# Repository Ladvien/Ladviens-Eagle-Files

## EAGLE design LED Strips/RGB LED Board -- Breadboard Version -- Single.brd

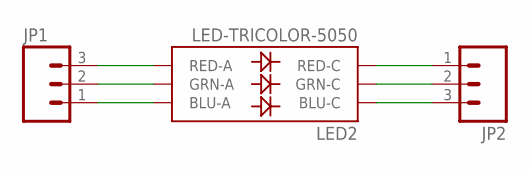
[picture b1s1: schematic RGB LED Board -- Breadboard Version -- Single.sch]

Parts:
JP1, JP2: M03PTH; 1X03
LED2: LED-TRICOLOR-5050

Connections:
unnamed: JP1.1, LED2.3 (BLU-A)
unnamed: JP1.2, LED2.1 (GRN-A)
unnamed: JP1.3, LED2.2 (RED-A)
unnamed: JP2.1, LED2.5 (RED-C)
unnamed: JP2.2, LED2.6 (GRN-C)
unnamed: JP2.3, LED2.4 (BLU-C)

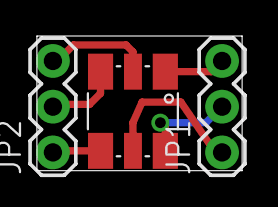
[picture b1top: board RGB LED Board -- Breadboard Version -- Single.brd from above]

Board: 2 copper layers, 11.4 x 7.5 mm, 3 parts (0 on the bottom side), 6 nets.

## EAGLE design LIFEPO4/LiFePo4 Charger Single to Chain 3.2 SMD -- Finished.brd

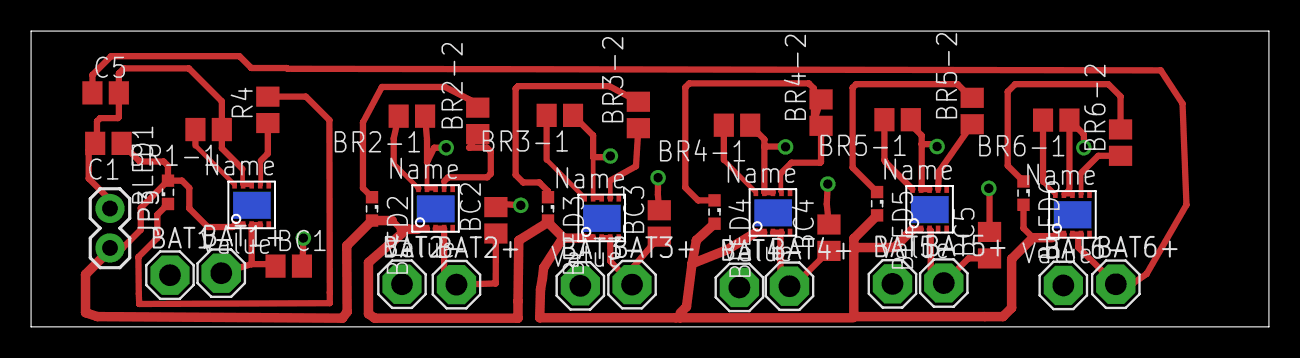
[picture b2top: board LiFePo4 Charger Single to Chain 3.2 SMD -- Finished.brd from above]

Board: 2 copper layers, 79.7 x 19.0 mm, 44 parts (0 on the bottom side), 26 nets.

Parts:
BAT1+, BAT1-, BAT2+, BAT2-, BAT3+, BAT3-, BAT4+, BAT4-, BAT5+, BAT5-, BAT6+, BAT6-: SE14
BC1, BC2, BC3, BC4, BC5: 4.7; C0805
BLED1, BLED2, BLED3, BLED4, BLED5, BLED6: 3.2v; SML0603
BR1-1, BR2-1, BR3-1, BR4-1, BR5-1, BR6-1: 1.5k; R0805
BR2-2, BR3-2, BR4-2, BR5-2, BR6-2: 1k; R0805
C1, C5: 4.7; C0805
IC2, IC4: MCP73123/223
JP3: Vraw/Grnd; 1X02
R4: 1k; R0805
U$1, U$3, U$5, U$8: MCP73123/223

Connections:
BC6: BAT6+.MP, C5.1, U$3.3, U$3.4
BR1-2: R4.1, U$1.7
GND: BAT1-.MP, BAT2-.MP, BAT3-.MP, BAT4-.MP, BAT5-.MP, BAT6-.MP, BC1.2, BC2.2, BC3.2, BC4.2, BC5.2, BR1-1.1, BR2-1.1, BR3-1.1, BR4-1.1, BR5-1.1, BR6-1.1, C1.2, C5.2, IC2.8, IC2.9, IC4.8, IC4.9, JP3.1, U$1.8, U$1.9, U$3.8, U$3.9, U$5.8, U$5.9, U$8.8, U$8.9
unnamed: BLED1.A, BLED2.A, BLED3.A, BLED4.A, BLED5.A, BLED6.A, C1.1, IC2.1, IC2.2, IC4.1, IC4.2, JP3.2, U$1.1, U$1.2, U$3.1, U$3.2, U$5.1, U$5.2, U$8.1, U$8.2
unnamed: BAT5+.MP, BC5.1, U$8.3
unnamed: BR5-1.2, U$8.10
unnamed: BLED5.C, BR5-2.2
unnamed: BR5-2.1, U$8.7
unnamed: BAT1+.MP, BC1.1, U$1.3, U$1.4
unnamed: BR1-1.2, U$1.10
unnamed: BAT2+.MP, BC2.1, IC2.3, IC2.4
unnamed: BLED1.C, R4.2
unnamed: BR2-2.1, IC2.7
unnamed: BR2-1.2, IC2.10
unnamed: BLED2.C, BR2-2.2
unnamed: BR6-2.1, U$3.7
unnamed: BR6-1.2, U$3.10
unnamed: BLED6.C, BR6-2.2
unnamed: BAT3+.MP, BC3.1, U$5.3, U$5.4
unnamed: BR3-2.1, U$5.7
unnamed: BR3-1.2, U$5.10
unnamed: BLED3.C, BR3-2.2
unnamed: BAT4+.MP, BC4.1, IC4.3, IC4.4
unnamed: BR4-2.1, IC4.7
unnamed: BR4-1.2, IC4.10
unnamed: BLED4.C, BR4-2.2

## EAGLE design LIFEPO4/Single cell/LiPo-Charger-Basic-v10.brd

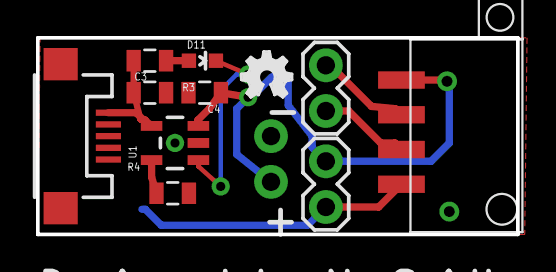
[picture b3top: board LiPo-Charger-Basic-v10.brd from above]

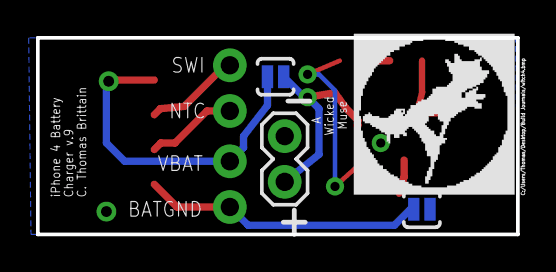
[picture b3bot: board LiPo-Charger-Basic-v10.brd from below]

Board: 2 copper layers, 26.7 x 10.9 mm, 15 parts (4 on the bottom side), 10 nets.

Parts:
C3, C4: 4.7uF; 0805
D11: RED; LED-0603
JP1, JP2, JP8: 1X02
R3: 330; 0805
R4: 2K; 0805
SJ1, SJ2: SOLDERJUMPERNO; SJ_2S-NO
U1: MCP73831; SOT23-5
U$1: IPHONE4_CONNECTOR
U$2: BAND_LOGO_SMALL
U$3: OSHW_FILLX100_NOTEXT
X1: Micro USB; USB-MICROB

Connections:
BATGND: JP1.1, SJ2.2, U$1.GND
GND: C3.2, C4.2, JP8.1, R4.2, SJ2.1, U1.2, X1.GND
unnamed: D11.A, R3.1
NTC: JP2.1, U$1.NTC
PROG: R4.1, U1.5
STAT: D11.C, U1.1
SWI: JP2.2, U$1.SWI
VBAT: JP1.2, SJ1.2, U$1.VBAT
VCC: C4.1, JP8.2, SJ1.1, U1.3
VIN: C3.1, R3.2, U1.4, X1.VBUS

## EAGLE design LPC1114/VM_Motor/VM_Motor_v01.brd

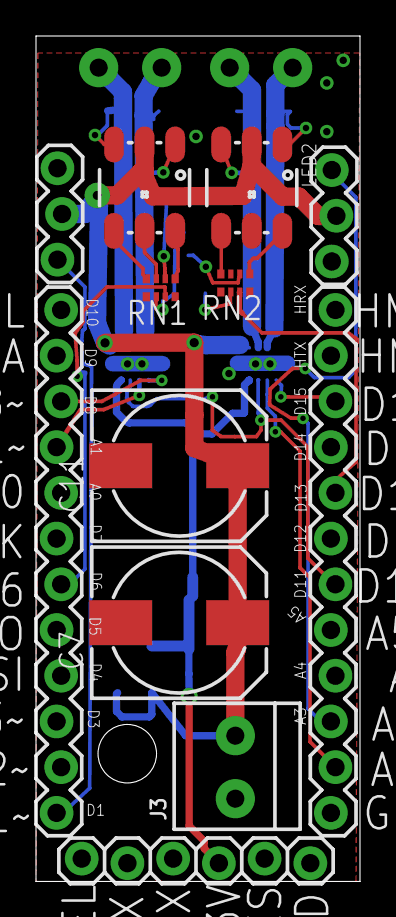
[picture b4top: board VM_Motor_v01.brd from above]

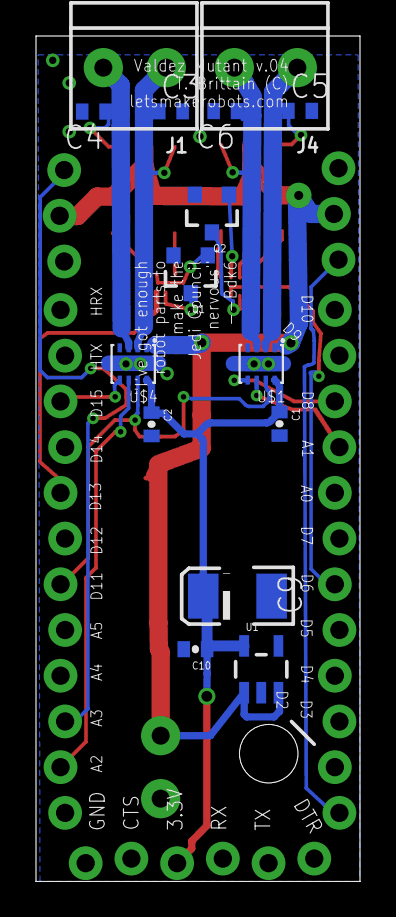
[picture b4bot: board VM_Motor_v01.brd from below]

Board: 2 copper layers, 18.0 x 47.0 mm, 30 parts (16 on the bottom side), 26 nets.

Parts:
C1, C2: 0402-CAP
C3, C4, C5, C6: 100nF; C0402
C7, C11: 140CLH-0810
C9: 100uF; EIA3528-KIT
C10: .1uF; 0402-CAP
FRAME1: FRAME-LETTER; CREATIVE_COMMONS
J1, J3, J4: TERMBLOCK_1X2-3.5MM
JP1, JP2: M12LOCK; 1X12_LOCK
JP3: 1X06_LOCK
JP4, JP5: 1X03_LOCK
LED1, LED2: LED-TRICOLOR-5050NO_IC; LED-TRICOLOR-5050
Q1, Q2: MMBT2222A; SOT23-3
RN1, RN2: 4X0402ARV341
U1: MIC5219 5V; SOT23-5
U$1, U$4: DRV8837; QFN8
U$2, U$3: OSHW_FILLX100_NOTEXT

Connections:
+5V: C1.1, C2.1, C9.A, C10.1, JP3.4, U1.5, U$1.P$8, U$4.P$8
GND: C1.2, C2.2, C3.2, C4.2, C5.2, C6.2, C7.-, C9.C, C10.2, C11.-, J3.2, JP2.1, JP3.6, JP4.3, JP5.1, Q1.2, Q2.2, RN1.1, RN1.4, RN2.1, RN2.4, U1.2, U$1.P$4, U$1.P$9, U$1.P$10, U$1.P$11, U$4.P$4, U$4.P$9, U$4.P$10, U$4.P$11
IO20: JP2.8, RN2.3
IO_07: JP1.6, RN1.3
IO_011: JP1.1, JP4.1
IO_13: JP2.3, JP5.3
MOTOR1_DIR: JP1.10, U$1.P$5
MOTOR1_PWM: JP1.9, U$1.P$6
MOTOR2_DIR: JP2.10, U$4.P$5
MOTOR2_PWM: JP2.2, U$4.P$6
MOUT1_A: C5.1, J4.2, LED1.3, U$1.P$2
MOUT1_B: C6.1, J4.1, LED1.1, U$1.P$3
MOUT2_A: C3.1, J1.2, LED2.3, U$4.P$2
MOUT2_B: C4.1, J1.1, LED2.1, U$4.P$3
unnamed: Q1.1, RN2.6
unnamed: LED1.4, RN1.8
unnamed: LED1.6, RN1.5
unnamed: LED2.4, RN2.8
unnamed: LED1.5, RN1.7
unnamed: Q1.3, RN2.2
unnamed: Q2.3, RN1.2
unnamed: Q2.1, RN1.6
unnamed: LED2.6, RN2.5
unnamed: LED2.5, RN2.7
SLEEP: JP2.6, U$1.P$7, U$4.P$7
VIN: C7.+, C11.+, J3.1, JP4.2, JP5.2, LED1.2, LED2.2, U1.1, U1.3, U$1.P$1, U$4.P$1

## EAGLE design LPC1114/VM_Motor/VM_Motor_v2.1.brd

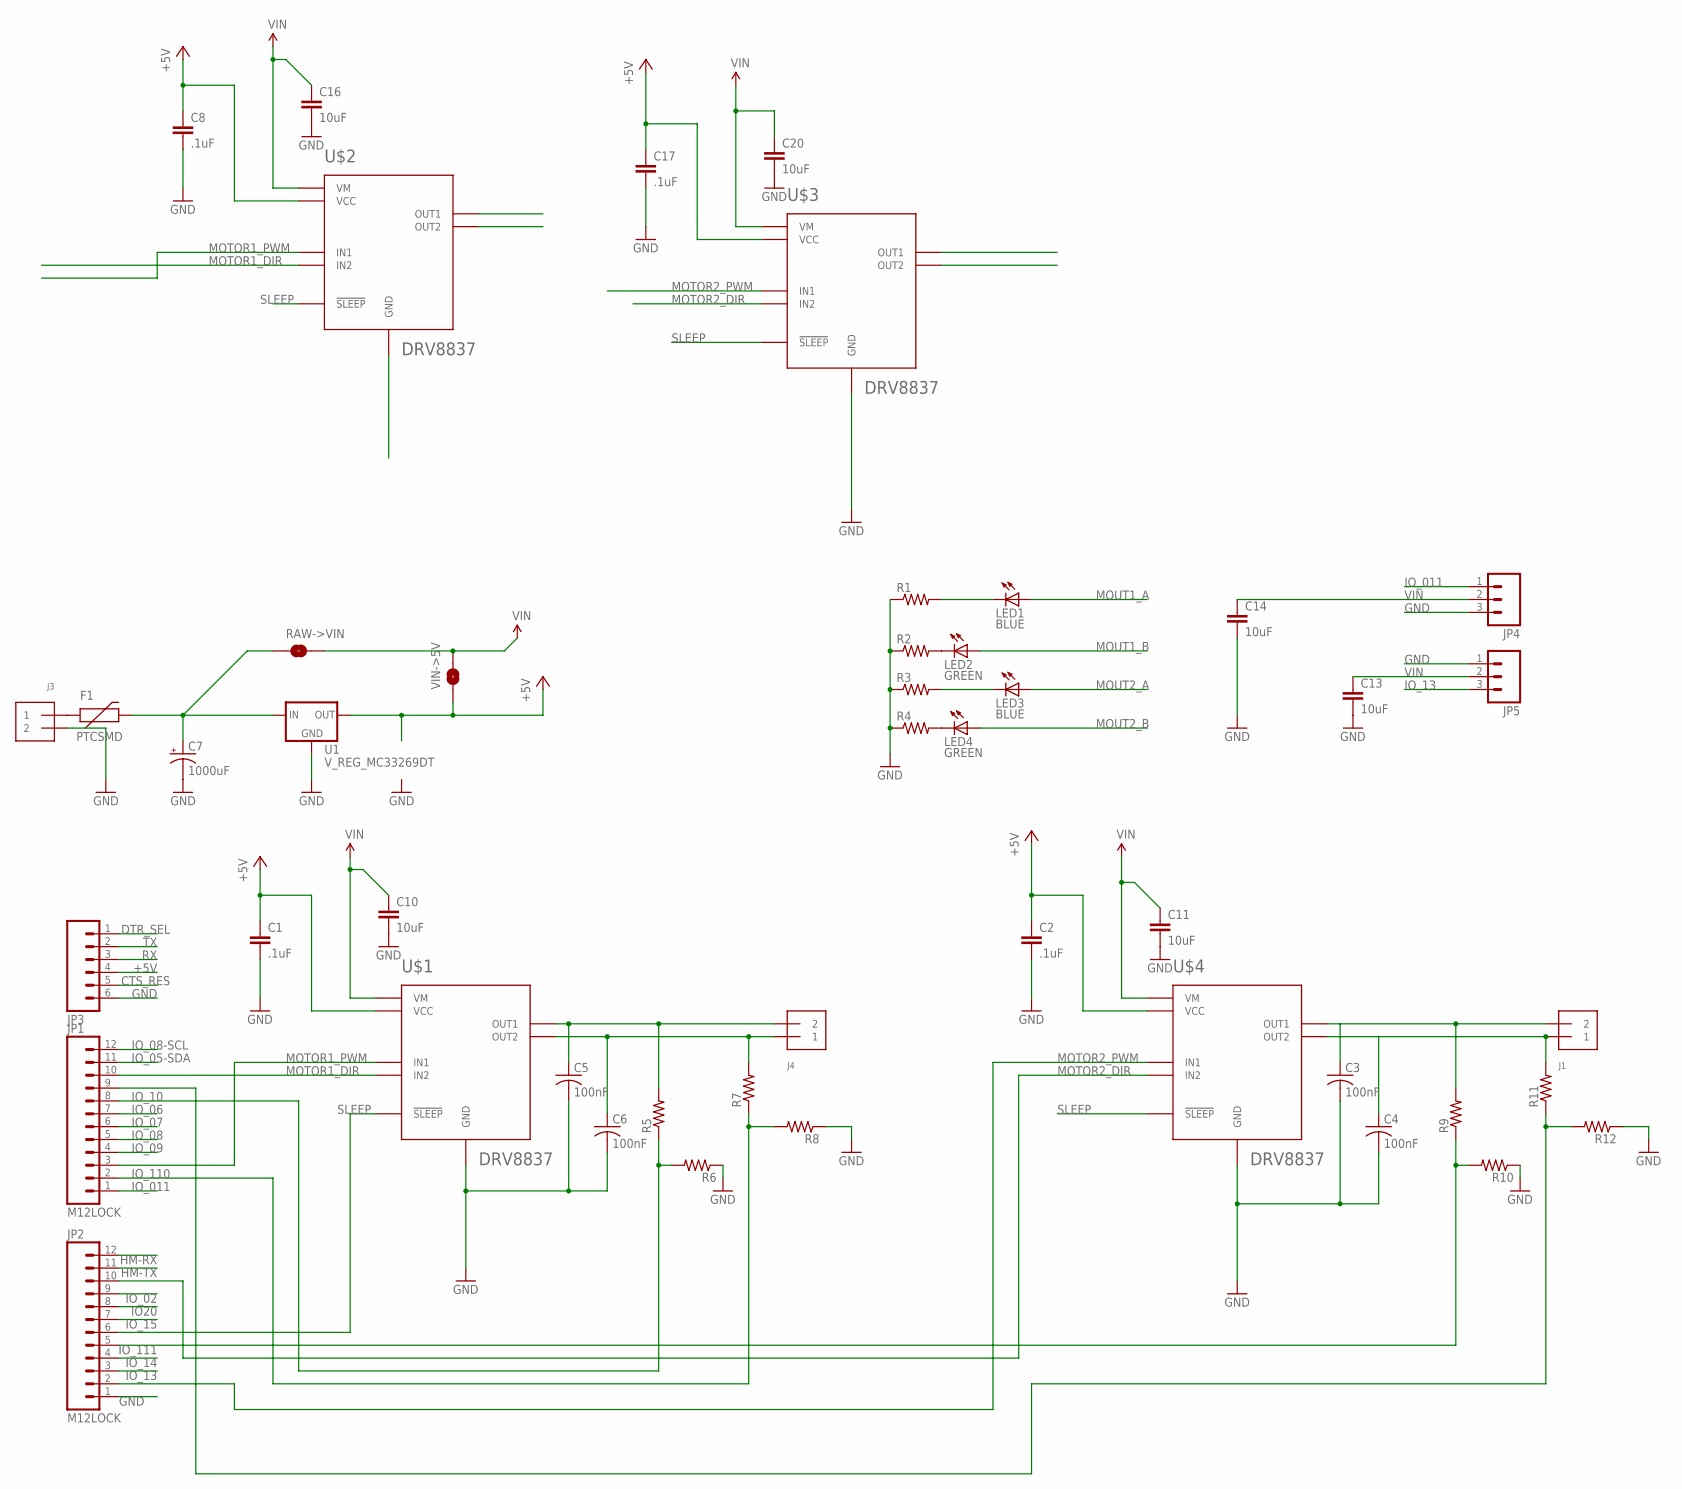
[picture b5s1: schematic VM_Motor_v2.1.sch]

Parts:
C1, C2, C8, C17: .1uF; 0402-CAP
C3, C4, C5, C6: 100nF; C0402
C7: 1000uF; 150CLZ-0810
C10, C11, C13, C14, C16, C20: 10uF; 0402-CAP
F1: PTCSMD; PTC-1206
J1, J3, J4: TERMBLOCK_1X2; TERMBLOCK_1X2-3.5MM
JP1, JP2: M12LOCK; 1X12_LOCK
JP3: M06LOCK; 1X06_LOCK
JP4, JP5: M03LOCK; 1X03_LOCK
LED1, LED3: BLUE; CHIP-LED0603
LED2, LED4: GREEN; CHIP-LED0603
R1, R2, R3, R4, R5, R6, R7, R8, R9, R10, R11, R12: R-US_R0402; R0402
RAW->VIN: SOLDERJUMPERNO; SJ_2S-NO
U1: V_REG_MC33269DT; DPAK
U$1, U$2, U$3, U$4: DRV8837; QFN8
VIN->5V: SOLDERJUMPERNO; SJ_2S-NO

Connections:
+5V: C1.1, C2.1, C8.1, C17.1, JP3.4, U1.4 (OUT), U$1.P$8 (VCC), U$2.P$8 (VCC), U$3.P$8 (VCC), U$4.P$8 (VCC), VIN->5V.1
CTS_RES: JP3.5
DTR_SEL: JP3.1
GND: C1.2, C2.2, C3.2, C4.2, C5.2, C6.2, C7.-, C8.2, C10.2, C11.2, C13.2, C14.2, C16.2, C17.2, C20.2, J3.2, JP2.1, JP3.6, JP4.3, JP5.1, R1.1, R2.1, R3.1, R4.1, R6.1, R8.1, R10.1, R12.1, U1.1 (GND), U$1.P$4 (GND), U$1.P$9 (GND), U$1.P$10 (GND), U$1.P$11 (GND), U$2.P$4 (GND), U$2.P$9 (GND), U$2.P$10 (GND), U$2.P$11 (GND), U$3.P$4 (GND), U$3.P$9 (GND), U$3.P$10 (GND), U$3.P$11 (GND), U$4.P$4 (GND), U$4.P$9 (GND), U$4.P$10 (GND), U$4.P$11 (GND)
HM-RX: JP2.12
HM-TX: JP2.11
IO20: JP2.8
IO_02: JP2.9
IO_05-SDA: JP1.11
IO_06: JP1.7
IO_07: JP1.6
IO_08: JP1.5
IO_08-SCL: JP1.12
IO_09: JP1.4
IO_10: JP1.8, R5.1, R6.2
IO_011: JP1.1, JP4.1
IO_11: JP1.9, R11.1, R12.2
IO_13: JP2.3, JP5.3
IO_14: JP2.4
IO_15: JP2.7
IO_110: JP1.2, R7.1, R8.2
IO_111: JP2.5, R9.1, R10.2
MOTOR1_DIR: JP1.10, U$1.P$5 (IN2), U$2.P$5 (IN2)
MOTOR1_PWM: JP1.3, U$1.P$6 (IN1), U$2.P$6 (IN1)
MOTOR2_DIR: JP2.10, U$3.P$5 (IN2), U$4.P$5 (IN2)
MOTOR2_PWM: JP2.2, U$3.P$6 (IN1), U$4.P$6 (IN1)
MOUT1_A: C5.1, J4.2, LED1.A, R5.2, U$1.P$2 (OUT1), U$2.P$2 (OUT1)
MOUT1_B: C6.1, J4.1, LED2.A, R7.2, U$1.P$3 (OUT2), U$2.P$3 (OUT2)
MOUT2_A: C3.1, J1.2, LED3.A, R9.2, U$3.P$2 (OUT1), U$4.P$2 (OUT1)
MOUT2_B: C4.1, J1.1, LED4.A, R11.2, U$3.P$3 (OUT2), U$4.P$3 (OUT2)
unnamed: LED2.C, R2.2
unnamed: LED4.C, R4.2
unnamed: LED1.C, R1.2
unnamed: LED3.C, R3.2
unnamed: F1.1, J3.1
RAW: C7.+, F1.2, RAW->VIN.1, U1.3 (IN)
RX: JP3.3
SLEEP: JP2.6, U$1.P$7 (!SLEEP), U$2.P$7 (!SLEEP), U$3.P$7 (!SLEEP), U$4.P$7 (!SLEEP)
TX: JP3.2
VIN: C10.1, C11.1, C13.1, C14.1, C16.1, C20.1, JP4.2, JP5.2, RAW->VIN.2, U$1.P$1 (VM), U$2.P$1 (VM), U$3.P$1 (VM), U$4.P$1 (VM), VIN->5V.2

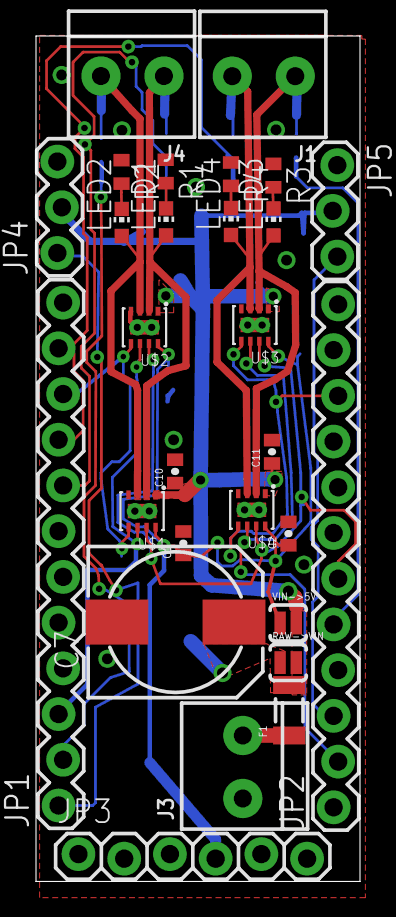
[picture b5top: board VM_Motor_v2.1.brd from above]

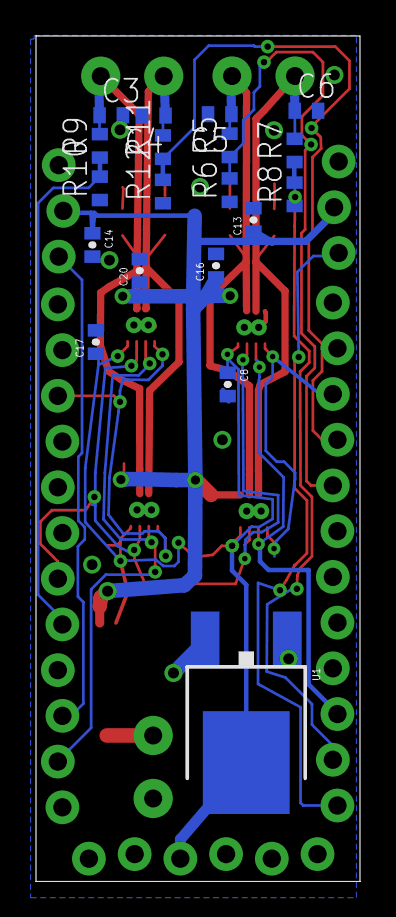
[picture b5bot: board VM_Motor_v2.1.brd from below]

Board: 2 copper layers, 18.0 x 47.0 mm, 47 parts (19 on the bottom side), 24 nets.

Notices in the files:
parts and their libraries:
SparkFun: Licensing: CC v3.0 Share-Alike You are welcome to use this library for commercial purposes.
SparkFun-Connectors: Licensing: Creative Commons ShareAlike 4.0 International - https://creativecommons.org/licenses/by-sa/4.0
SparkFun-Aesthetics: https://creativecommons.org/licenses/by-sa/4.0
